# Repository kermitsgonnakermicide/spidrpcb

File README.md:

# Spooder motor controller

This repository contains the KiCad work for a four-channel brushed motor controller. The proposed controller uses an RP2354B, four TI DRV8256P H-bridges, quadrature encoder inputs, USB-C device power, and a protected Feetech-style TTL serial-servo port.

The current KiCad sheets are still being edited. The design guide below is a reviewed target architecture, not a claim that the existing PCB already implements it.

## Design documents

- [Design guide](docs/rp2354-motor-controller/DESIGN_GUIDE.md)
- [Bill of materials](docs/rp2354-motor-controller/BOM.md)
- [RP2354B pin map](docs/rp2354-motor-controller/PIN_MAP.md)
- [Assembly and bring-up](docs/rp2354-motor-controller/ASSEMBLY_AND_BRINGUP.md)
- `docs/rp2354-motor-controller/SCHEMATIC.jsx` is the rendered architecture and reference-circuit sheet.

## Target specification

| Item | Target |
| --- | --- |
| MCU | RP2354B, QFN-80, 2 MB in-package flash |
| Brushed motors | 4 independent channels |
| Driver | 4 × DRV8256PRGER |
| Motor supply | External regulated 6 V or 12 V, 12.6 V maximum |
| Per-motor limit | 2.0 A nominal hardware chopping threshold |
| Encoders | 4 × 5 V quadrature Hall encoders |
| USB-C | USB 2.0 device and logic power only |
| Smart servos | Feetech/Waveshare ST/SC TTL half-duplex bus |

Do not power motors or servos from USB VBUS. USB ground and motor ground join on the controller, but their high-current return paths must stay separate until the power-entry star point.

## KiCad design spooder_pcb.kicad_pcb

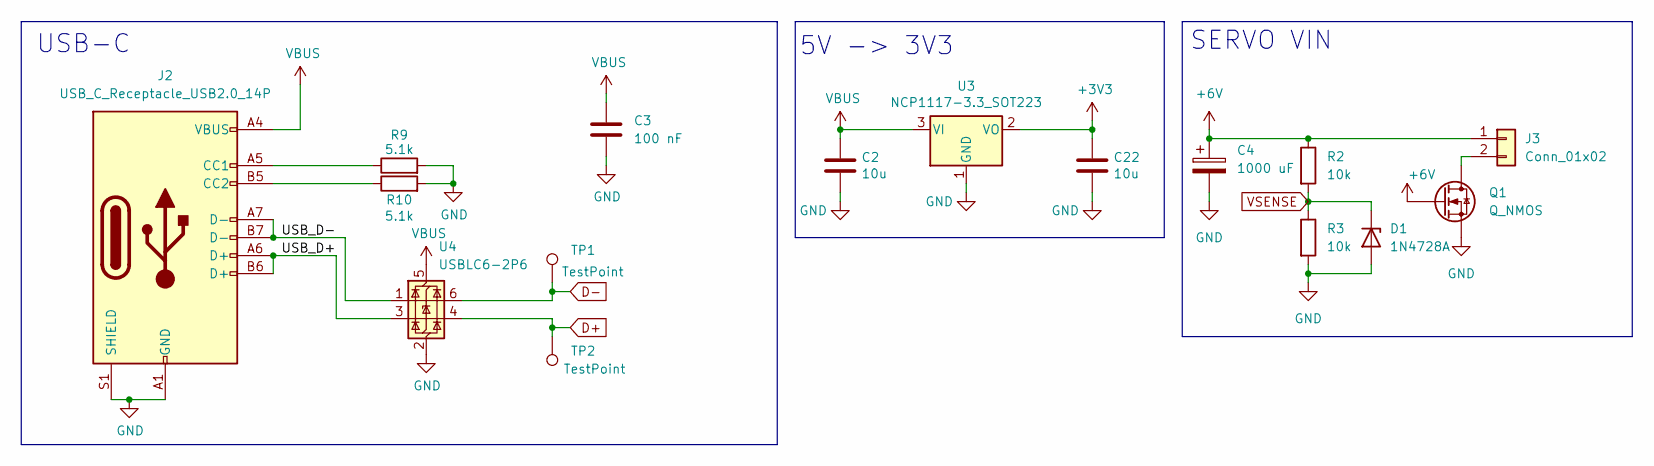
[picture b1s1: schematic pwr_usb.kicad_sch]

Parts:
C2, C22: 10u; C_0805_2012Metric
C3: 100 nF; C_0402_1005Metric
C4: 1000 uF; CP_Radial_D10.0mm_P5.00mm
D1: 1N4728A; D_DO-41_SOD81_P10.16mm_Horizontal
J2: USB_C_Receptacle_USB2.0_14P; USB_C_Receptacle_Molex_105450-0101
J3: Conn_01x02; PinHeader_1x02_P2.54mm_Vertical
Q1: Q_NMOS
R2, R3: 10k; R_0805_2012Metric
R9, R10: 5.1k; R_0603_1608Metric
TP1, TP2: TestPoint; TestPoint_Plated_Hole_D3.0mm
U3: NCP1117-3.3_SOT223; SOT-223-3_TabPin2
U4: USBLC6-2P6; SOT-666

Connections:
+3V3: C22.1, U3.2 (VO); also elsewhere on the board
+6V: C4.1, J3.1, Q1.G, R2.1; also elsewhere on the board
/pwr_usb/USB_D+: J2.A6 (D+), J2.B6 (D+), U4.3 (I/O2)
/pwr_usb/USB_D-: J2.A7 (D-), J2.B7 (D-), U4.1 (I/O1)
D+: TP2.1, U4.4 (I/O2); also elsewhere on the board
D-: TP1.1, U4.6 (I/O1); also elsewhere on the board
GND: C2.2, C3.2, C4.2, C22.2, D1.2 (A), J2.A1 (GND), J2.A12 (GND), J2.B1 (GND), J2.B12 (GND), J2.S1 (SHIELD), Q1.S, R3.2, R9.2, R10.2, U3.1 (GND), U4.2 (GND); also elsewhere on the board
unnamed: J2.A5 (CC1), R9.1
unnamed: J2.B5 (CC2), R10.1
unnamed: J3.2, Q1.D
VBUS: C2.1, C3.1, J2.A4 (VBUS), J2.A9 (VBUS), J2.B4 (VBUS), J2.B9 (VBUS), U3.3 (VI), U4.5 (VBUS)
VSENSE: D1.1 (K), R2.2, R3.1

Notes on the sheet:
5V -> 3V3
SERVO VIN
USB-C

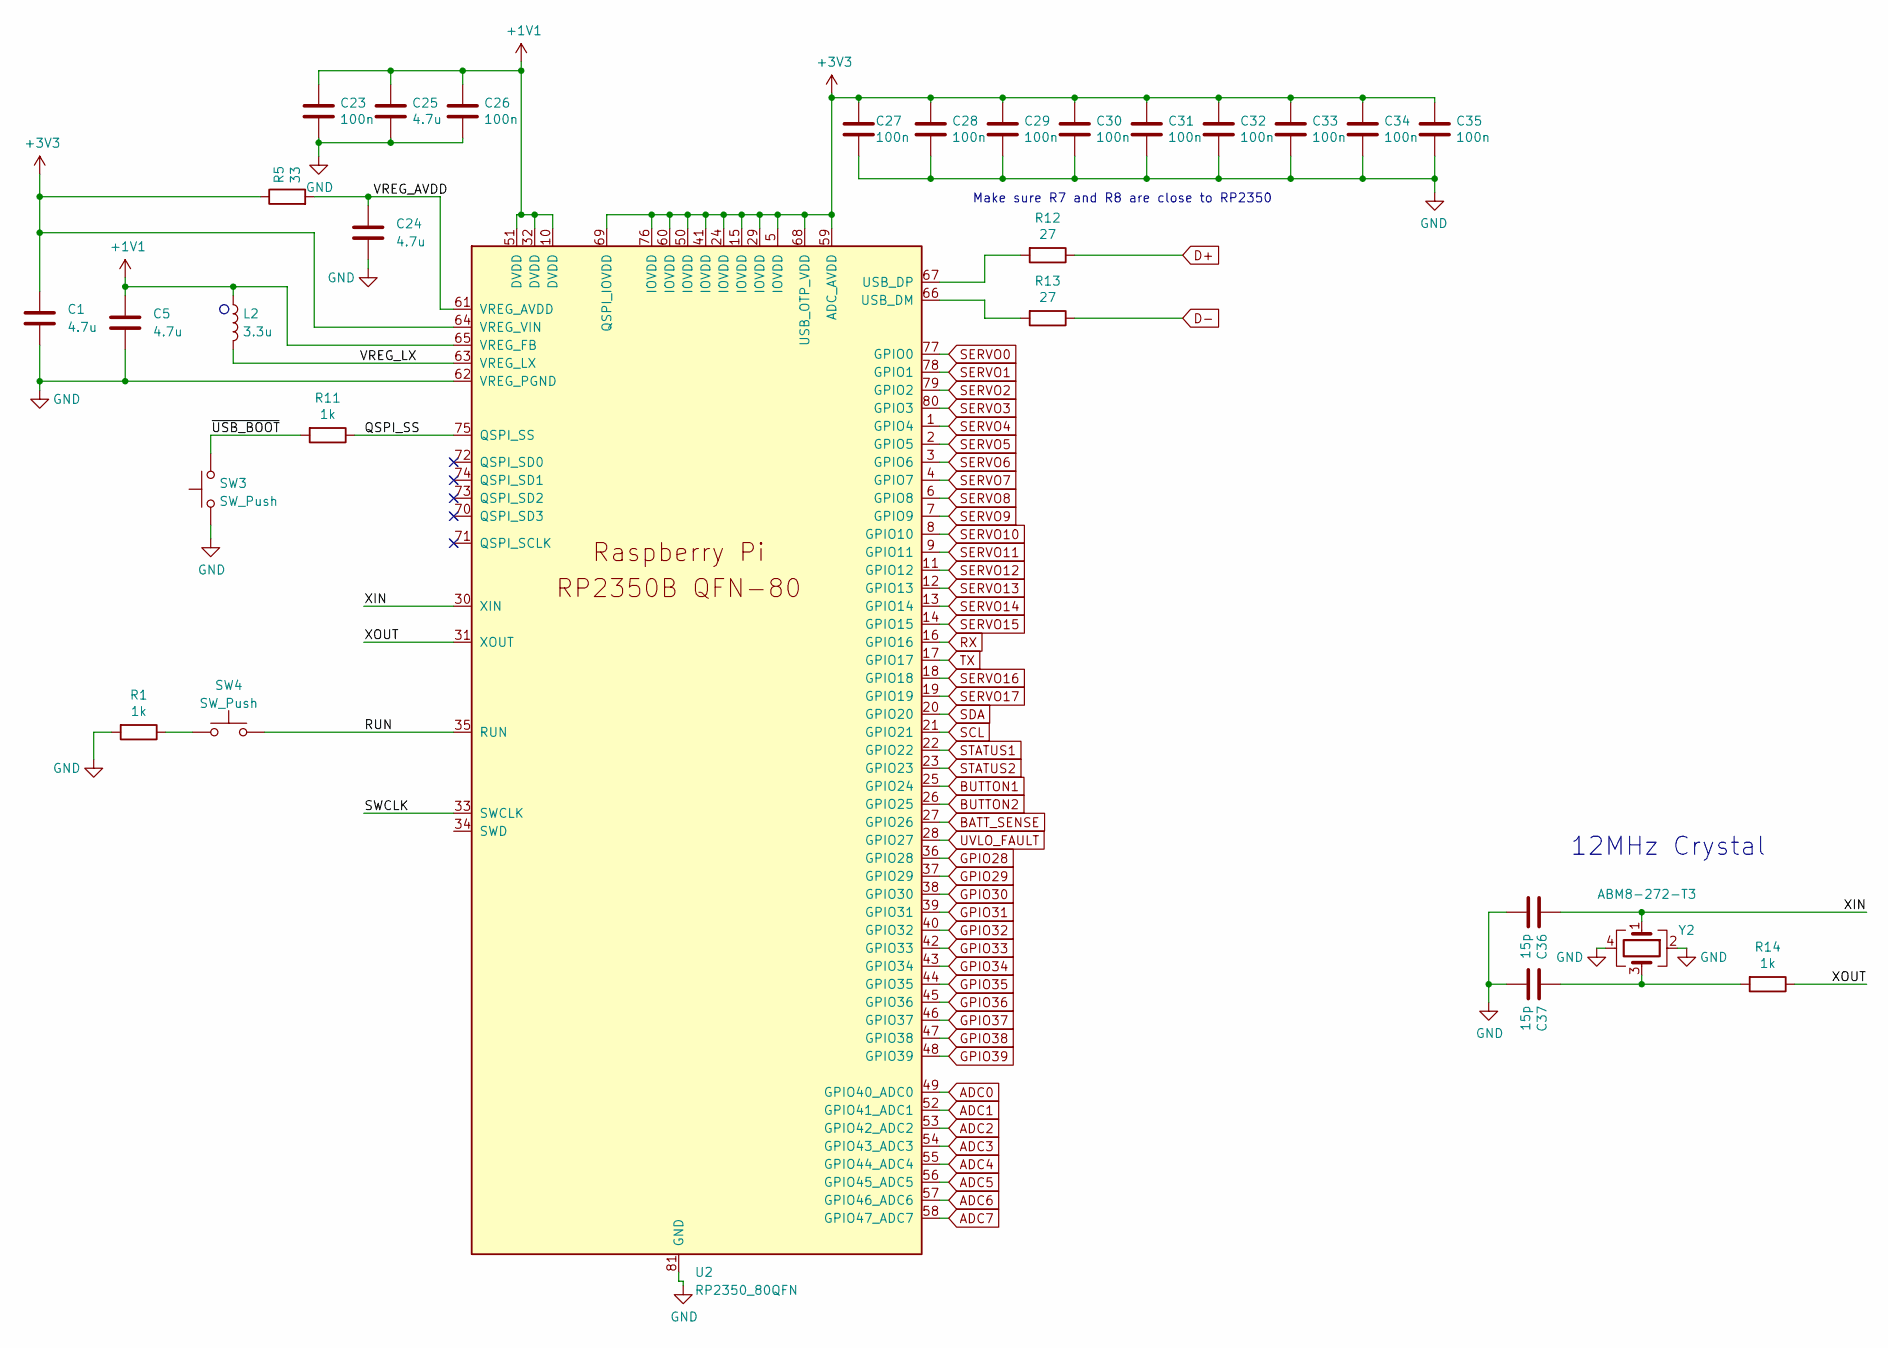
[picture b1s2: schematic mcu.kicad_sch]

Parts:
C1, C5: 4.7u; C_0402_1005Metric_small_pads
C23, C26, C27, C28, C29, C30, C31, C32, C33, C34, C35: 100n; C_0402_1005Metric
C24, C25: 4.7u; C_0402_1005Metric
C36, C37: 15p; C_0402_1005Metric
L2: 3.3u; L_pol_2016
R1, R11, R14: 1k; R_0402_1005Metric
R5: 33; R_0402_1005Metric
R12, R13: 27; R_0402_1005Metric
SW3, SW4: SW_Push; SW_Push_1P1T_NO_Vertical_Wuerth_434133025816
U2: RP2350_80QFN; RP2350-QFN-80-1EP_10x10_P0.4mm_EP3.4x3.4mm_ThermalVias
Y2: ABM8-272-T3; Crystal_SMD_3225-4Pin_3.2x2.5mm

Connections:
+1V1: C5.1, C23.1, C25.1, C26.1, L2.1, U2.10 (DVDD), U2.32 (DVDD), U2.51 (DVDD), U2.65 (VREG_FB)
+3V3: C1.1, C27.1, C28.1, C29.1, C30.1, C31.1, C32.1, C33.1, C34.1, C35.1, R5.1, U2.5 (IOVDD), U2.15 (IOVDD), U2.24 (IOVDD), U2.29 (IOVDD), U2.41 (IOVDD), U2.50 (IOVDD), U2.59 (ADC_AVDD), U2.60 (IOVDD), U2.64 (VREG_VIN), U2.68 (USB_OTP_VDD), U2.69 (QSPI_IOVDD), U2.76 (IOVDD); also elsewhere on the board
/MCU/QSPI_SS: R11.1, U2.75 (QSPI_SS)
/MCU/RUN: SW4.2, U2.35 (RUN)
/MCU/SWCLK: U2.33 (SWCLK)
/MCU/VREG_AVDD: C24.1, R5.2, U2.61 (VREG_AVDD)
/MCU/VREG_LX: L2.2, U2.63 (VREG_LX)
/MCU/XIN: C36.1, U2.30 (XIN), Y2.1
/MCU/XOUT: R14.1, U2.31 (XOUT)
/MCU/~USB_BOOT: R11.2, SW3.2
ADC0: U2.49 (GPIO40_ADC0)
ADC1: U2.52 (GPIO41_ADC1)
ADC2: U2.53 (GPIO42_ADC2)
ADC3: U2.54 (GPIO43_ADC3)
ADC4: U2.55 (GPIO44_ADC4)
ADC5: U2.56 (GPIO45_ADC5)
ADC6: U2.57 (GPIO46_ADC6)
ADC7: U2.58 (GPIO47_ADC7)
BATT_SENSE: U2.27 (GPIO26); also elsewhere on the board
BUTTON1: U2.25 (GPIO24); also elsewhere on the board
BUTTON2: U2.26 (GPIO25); also elsewhere on the board
D+: R12.1; also elsewhere on the board
D-: R13.1; also elsewhere on the board
GND: C1.2, C5.2, C23.2, C24.2, C25.2, C26.2, C27.2, C28.2, C29.2, C30.2, C31.2, C32.2, C33.2, C34.2, C35.2, C36.2, C37.2, R1.2, SW3.1, U2.62 (VREG_PGND), U2.81 (GND), Y2.2, Y2.4; also elsewhere on the board
GPIO28: U2.36 (GPIO28)
GPIO29: U2.37 (GPIO29)
GPIO30: U2.38 (GPIO30); also elsewhere on the board
GPIO31: U2.39 (GPIO31); also elsewhere on the board
GPIO32: U2.40 (GPIO32); also elsewhere on the board
GPIO33: U2.42 (GPIO33); also elsewhere on the board
GPIO34: U2.43 (GPIO34); also elsewhere on the board
GPIO35: U2.44 (GPIO35); also elsewhere on the board
GPIO36: U2.45 (GPIO36); also elsewhere on the board
GPIO37: U2.46 (GPIO37); also elsewhere on the board
GPIO38: U2.47 (GPIO38); also elsewhere on the board
GPIO39: U2.48 (GPIO39); also elsewhere on the board
unnamed: C37.1, R14.2, Y2.3
unnamed: R1.1, SW4.1
unnamed: R13.2, U2.66 (USB_DM)
unnamed: R12.2, U2.67 (USB_DP)
RX: U2.16 (GPIO16); also elsewhere on the board
SCL: U2.21 (GPIO21); also elsewhere on the board
SDA: U2.20 (GPIO20); also elsewhere on the board
SERVO0: U2.77 (GPIO0)
SERVO1: U2.78 (GPIO1)
SERVO2: U2.79 (GPIO2)
SERVO3: U2.80 (GPIO3)
SERVO4: U2.1 (GPIO4)
SERVO5: U2.2 (GPIO5)
SERVO6: U2.3 (GPIO6)
SERVO7: U2.4 (GPIO7)
SERVO8: U2.6 (GPIO8)
SERVO9: U2.7 (GPIO9)
SERVO10: U2.8 (GPIO10)
SERVO11: U2.9 (GPIO11)
SERVO12: U2.11 (GPIO12)
SERVO13: U2.12 (GPIO13)
SERVO14: U2.13 (GPIO14)
SERVO15: U2.14 (GPIO15)
SERVO16: U2.18 (GPIO18)
SERVO17: U2.19 (GPIO19)
STATUS1: U2.22 (GPIO22); also elsewhere on the board
STATUS2: U2.23 (GPIO23); also elsewhere on the board
TX: U2.17 (GPIO17); also elsewhere on the board
UVLO_FAULT: U2.28 (GPIO27); also elsewhere on the board

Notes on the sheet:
12MHz Crystal
Make sure R7 and R8 are close to RP2350

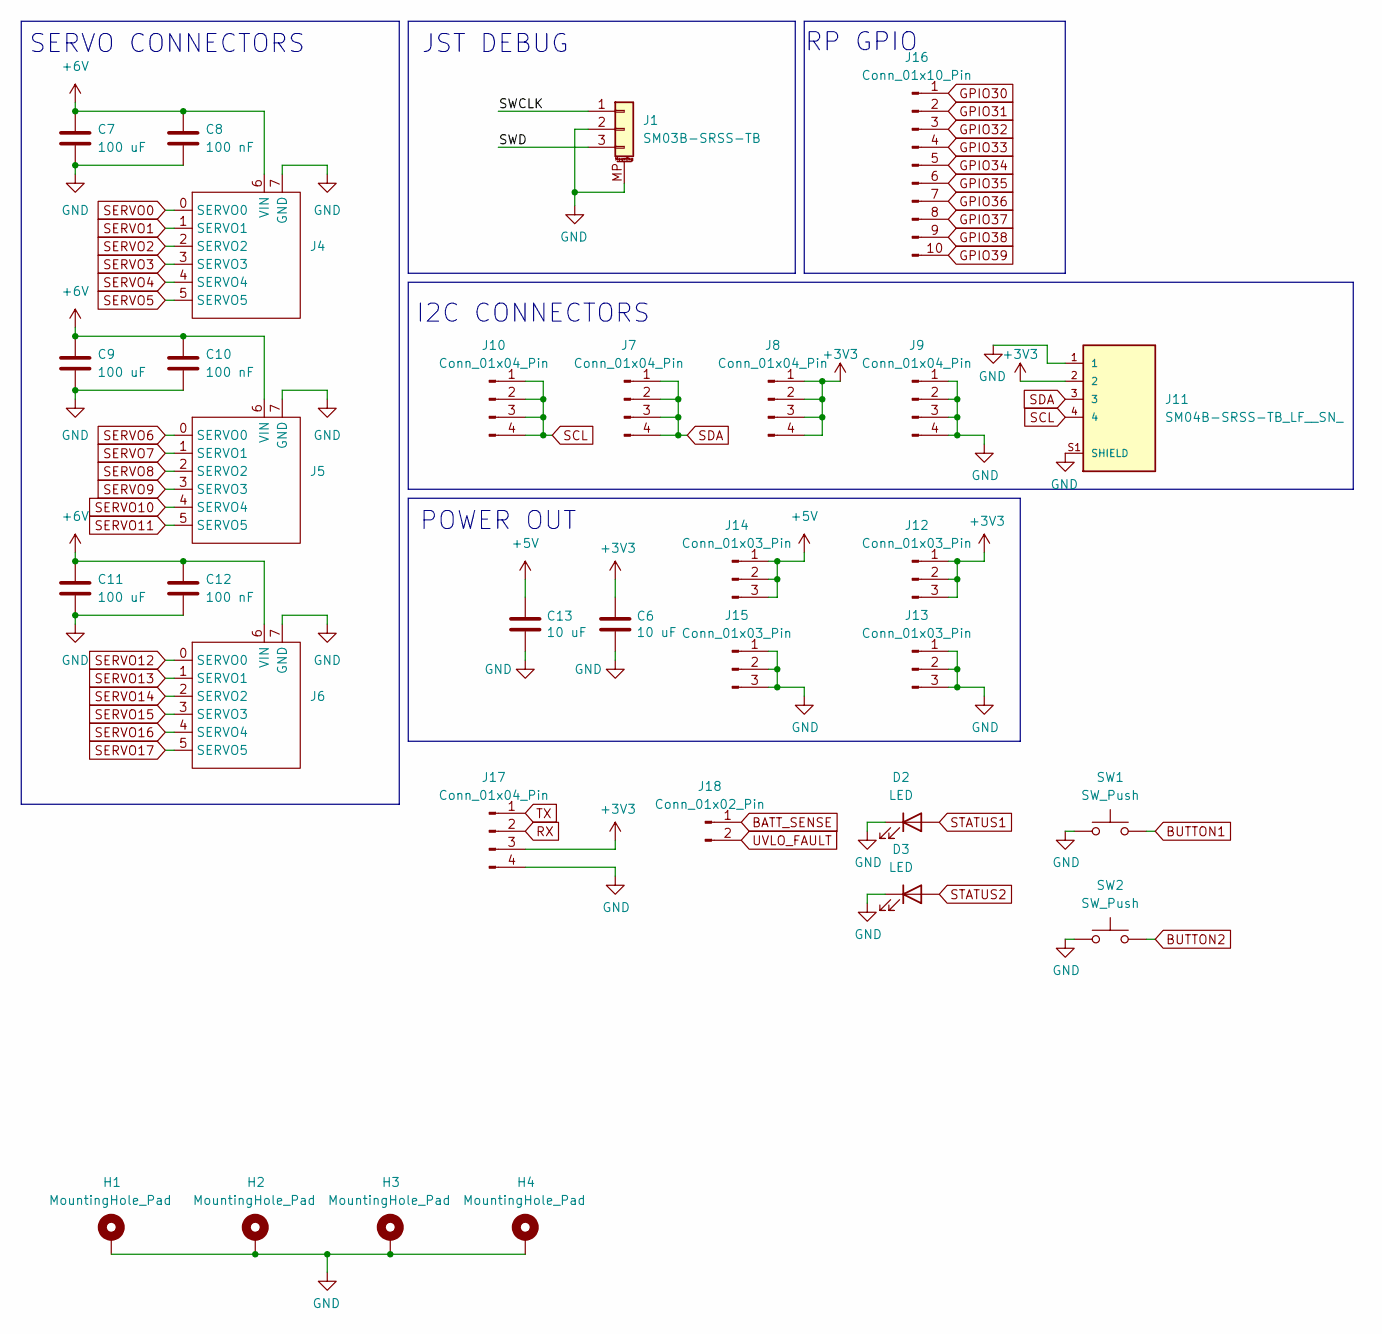
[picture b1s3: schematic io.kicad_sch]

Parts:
C6, C13: 10 uF; C_0805_2012Metric
C7, C9, C11: 100 uF; CP_Radial_D5.0mm_P2.00mm
C8, C10, C12: 100 nF; C_0402_1005Metric
D2, D3: LED; LED_1206_3216Metric
H1, H2, H3, H4: MountingHole_Pad; MountingHole_3.2mm_M3_Pad
J1: SM03B-SRSS-TB; JST_SH_SM03B-SRSS-TB_1x03-1MP_P1.00mm_Horizontal
J4, J5, J6: (no value)
J7, J8, J9, J10, J17: Conn_01x04_Pin; PinHeader_1x04_P2.54mm_Vertical
J11: SM04B-SRSS-TB_LF__SN_; JST_SM04B-SRSS-TB_LF__SN_
J12, J13, J14, J15: Conn_01x03_Pin; PinHeader_1x03_P2.54mm_Vertical
J16: Conn_01x10_Pin; PinHeader_1x10_P2.54mm_Vertical
J18: Conn_01x02_Pin; PinHeader_1x02_P2.54mm_Vertical
SW1, SW2: SW_Push; SW_Push_1P1T_NO_Vertical_Wuerth_434133025816

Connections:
+3V3: C6.1, J8.1, J8.2, J8.3, J8.4, J11.2, J12.1, J12.2, J12.3, J17.3; also elsewhere on the board
+5V: C13.1, J14.1, J14.2, J14.3
+6V: C7.1, C8.1, C9.1, C10.1, C11.1, C12.1, J4.6 (VIN), J5.6 (VIN), J6.6 (VIN); also elsewhere on the board
/io/SWCLK: J1.1
/io/SWD: J1.3
BATT_SENSE: J18.1; also elsewhere on the board
BUTTON1: SW1.2; also elsewhere on the board
BUTTON2: SW2.2; also elsewhere on the board
GND: C6.2, C7.2, C8.2, C9.2, C10.2, C11.2, C12.2, C13.2, D2.1 (K), D3.1 (K), H1.1, H2.1, H3.1, H4.1, J1.2, J1.MP (MountPin), J4.7 (GND), J5.7 (GND), J6.7 (GND), J9.1, J9.2, J9.3, J9.4, J11.1, J11.S1 (SHIELD), J11.S2 (SHIELD), J13.1, J13.2, J13.3, J15.1, J15.2, J15.3, J17.4, SW1.1, SW2.1; also elsewhere on the board
GPIO30: J16.1; also elsewhere on the board
GPIO31: J16.2; also elsewhere on the board
GPIO32: J16.3; also elsewhere on the board
GPIO33: J16.4; also elsewhere on the board
GPIO34: J16.5; also elsewhere on the board
GPIO35: J16.6; also elsewhere on the board
GPIO36: J16.7; also elsewhere on the board
GPIO37: J16.8; also elsewhere on the board
GPIO38: J16.9; also elsewhere on the board
GPIO39: J16.10; also elsewhere on the board
RX: J17.2; also elsewhere on the board
SCL: J10.1, J10.2, J10.3, J10.4, J11.4; also elsewhere on the board
SDA: J7.1, J7.2, J7.3, J7.4, J11.3; also elsewhere on the board
STATUS1: D2.2 (A); also elsewhere on the board
STATUS2: D3.2 (A); also elsewhere on the board
TX: J17.1; also elsewhere on the board
UVLO_FAULT: J18.2; also elsewhere on the board

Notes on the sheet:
POWER OUT
RP GPIO
I2C CONNECTORS
JST DEBUG
SERVO CONNECTORS

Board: 2 copper layers, 72 parts (0 on the bottom side), 44 nets, no tracks yet.
